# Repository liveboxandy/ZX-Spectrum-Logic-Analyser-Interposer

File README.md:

# ZX-Spectrum-Logic-Analyser-Interposer
Based on the design by HappyLittleDiodes but free form connections

Layout and connections completely redone so as to allow any logic signal on the edge connector or elsewhere to be connected to any Logic Analyser channel.

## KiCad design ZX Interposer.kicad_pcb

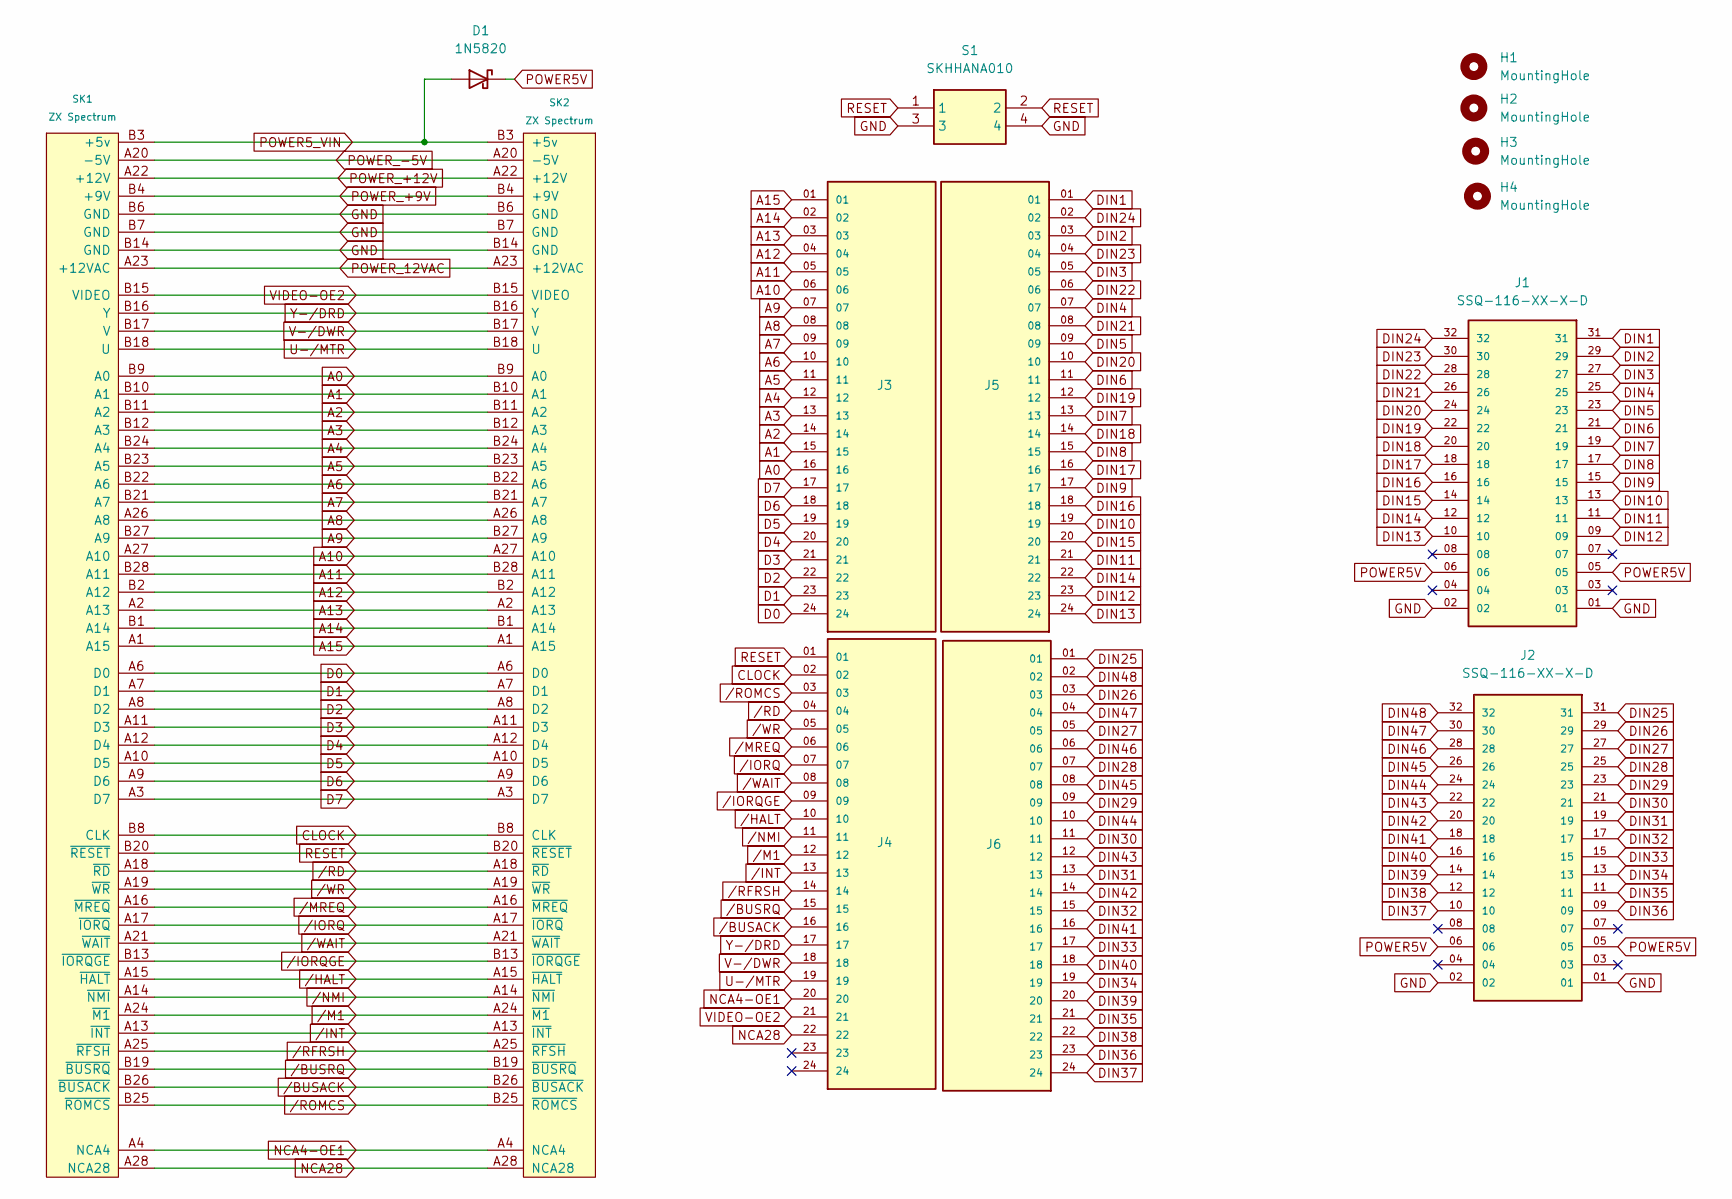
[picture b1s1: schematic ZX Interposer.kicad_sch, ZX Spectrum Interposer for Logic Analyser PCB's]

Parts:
D1: 1N5820; D_DO-201AD_P15.24mm_Horizontal
H1, H2, H3, H4: MountingHole; MountingHole_2.5mm
J1, J2: SSQ-116-XX-X-D; SAMTEC_SSQ-116-XX-X-D; PARTREV A
J3, J4, J5, J6: TSW-124-07-L-S; SAMTEC_TSW-124-07-L-S; PARTREV R
S1: SKHHANA010; Mouser Part Number 688-SKHHAN
SK1, SK2: ZX Spectrum; ZX_Spectrum_BUS_Edge_Connector Horizontal

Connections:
A0: J3.16, SK1.B9 (A0), SK2.B9 (A0)
A1: J3.15, SK1.B10 (A1), SK2.B10 (A1)
A2: J3.14, SK1.B11 (A2), SK2.B11 (A2)
A3: J3.13, SK1.B12 (A3), SK2.B12 (A3)
A4: J3.12, SK1.B24 (A4), SK2.B24 (A4)
A5: J3.11, SK1.B23 (A5), SK2.B23 (A5)
A6: J3.10, SK1.B22 (A6), SK2.B22 (A6)
A7: J3.09, SK1.B21 (A7), SK2.B21 (A7)
A8: J3.08, SK1.A26 (A8), SK2.A26 (A8)
A9: J3.07, SK1.B27 (A9), SK2.B27 (A9)
A10: J3.06, SK1.A27 (A10), SK2.A27 (A10)
A11: J3.05, SK1.B28 (A11), SK2.B28 (A11)
A12: J3.04, SK1.B2 (A12), SK2.B2 (A12)
A13: J3.03, SK1.A2 (A13), SK2.A2 (A13)
A14: J3.02, SK1.B1 (A14), SK2.B1 (A14)
A15: J3.01, SK1.A1 (A15), SK2.A1 (A15)
CLOCK: J4.02, SK1.B8 (CLK), SK2.B8 (CLK)
D0: J3.24, SK1.A6 (D0), SK2.A6 (D0)
D1: J3.23, SK1.A7 (D1), SK2.A7 (D1)
D2: J3.22, SK1.A8 (D2), SK2.A8 (D2)
D3: J3.21, SK1.A11 (D3), SK2.A11 (D3)
D4: J3.20, SK1.A12 (D4), SK2.A12 (D4)
D5: J3.19, SK1.A10 (D5), SK2.A10 (D5)
D6: J3.18, SK1.A9 (D6), SK2.A9 (D6)
D7: J3.17, SK1.A3 (D7), SK2.A3 (D7)
DIN1: J1.31, J5.01
DIN2: J1.29, J5.03
DIN3: J1.27, J5.05
DIN4: J1.25, J5.07
DIN5: J1.23, J5.09
DIN6: J1.21, J5.11
DIN7: J1.19, J5.13
DIN8: J1.17, J5.15
DIN9: J1.15, J5.17
DIN10: J1.13, J5.19
DIN11: J1.11, J5.21
DIN12: J1.09, J5.23
DIN13: J1.10, J5.24
DIN14: J1.12, J5.22
DIN15: J1.14, J5.20
DIN16: J1.16, J5.18
DIN17: J1.18, J5.16
DIN18: J1.20, J5.14
DIN19: J1.22, J5.12
DIN20: J1.24, J5.10
DIN21: J1.26, J5.08
DIN22: J1.28, J5.06
DIN23: J1.30, J5.04
DIN24: J1.32, J5.02
DIN25: J2.31, J6.01
DIN26: J2.29, J6.03
DIN27: J2.27, J6.05
DIN28: J2.25, J6.07
DIN29: J2.23, J6.09
DIN30: J2.21, J6.11
DIN31: J2.19, J6.13
DIN32: J2.17, J6.15
DIN33: J2.15, J6.17
DIN34: J2.13, J6.19
DIN35: J2.11, J6.21
DIN36: J2.09, J6.23
DIN37: J2.10, J6.24
DIN38: J2.12, J6.22
DIN39: J2.14, J6.20
DIN40: J2.16, J6.18
DIN41: J2.18, J6.16
DIN42: J2.20, J6.14
DIN43: J2.22, J6.12
DIN44: J2.24, J6.10
DIN45: J2.26, J6.08
DIN46: J2.28, J6.06
DIN47: J2.30, J6.04
DIN48: J2.32, J6.02
GND: J1.01, J1.02, J2.01, J2.02, S1.3, S1.4, SK1.B6 (GND), SK1.B7 (GND), SK1.B14 (GND), SK2.B6 (GND), SK2.B7 (GND), SK2.B14 (GND)
NCA4-OE1: J4.20, SK1.A4 (NCA4), SK2.A4 (NCA4)
NCA28: J4.22, SK1.A28 (NCA28), SK2.A28 (NCA28)
POWER5V: D1.1 (K), J1.05, J1.06, J2.05, J2.06
POWER5_VIN: D1.2 (A), SK1.B3 (+5v), SK2.B3 (+5v)
POWER_12VAC: SK1.A23 (+12VAC), SK2.A23 (+12VAC)
POWER_+9V: SK1.B4 (+9V), SK2.B4 (+9V)
POWER_+12V: SK1.A22 (+12V), SK2.A22 (+12V)
POWER_-5V: SK1.A20 (-5V), SK2.A20 (-5V)
RESET: J4.01, S1.1, S1.2, SK1.B20 (~RESET), SK2.B20 (~RESET)
U-/MTR: J4.19, SK1.B18 (U), SK2.B18 (U)
V-/DWR: J4.18, SK1.B17 (V), SK2.B17 (V)
VIDEO-OE2: J4.21, SK1.B15 (VIDEO), SK2.B15 (VIDEO)
Y-/DRD: J4.17, SK1.B16 (Y), SK2.B16 (Y)
/BUSACK: J4.16, SK1.B26 (~BUSACK), SK2.B26 (~BUSACK)
/BUSRQ: J4.15, SK1.B19 (~BUSRQ), SK2.B19 (~BUSRQ)
/HALT: J4.10, SK1.A15 (~HALT), SK2.A15 (~HALT)
/INT: J4.13, SK1.A13 (~INT), SK2.A13 (~INT)
/IORQ: J4.07, SK1.A17 (~IORQ), SK2.A17 (~IORQ)
/IORQGE: J4.09, SK1.B13 (~IORQGE), SK2.B13 (~IORQGE)
/M1: J4.12, SK1.A24 (~M1), SK2.A24 (~M1)
/MREQ: J4.06, SK1.A16 (~MREQ), SK2.A16 (~MREQ)
/NMI: J4.11, SK1.A14 (~NMI), SK2.A14 (~NMI)
/RD: J4.04, SK1.A18 (~RD), SK2.A18 (~RD)
/RFRSH: J4.14, SK1.A25 (~RFSH), SK2.A25 (~RFSH)
/ROMCS: J4.03, SK1.B25 (~ROMCS), SK2.B25 (~ROMCS)
/WAIT: J4.08, SK1.A21 (~WAIT), SK2.A21 (~WAIT)
/WR: J4.05, SK1.A19 (~WR), SK2.A19 (~WR)

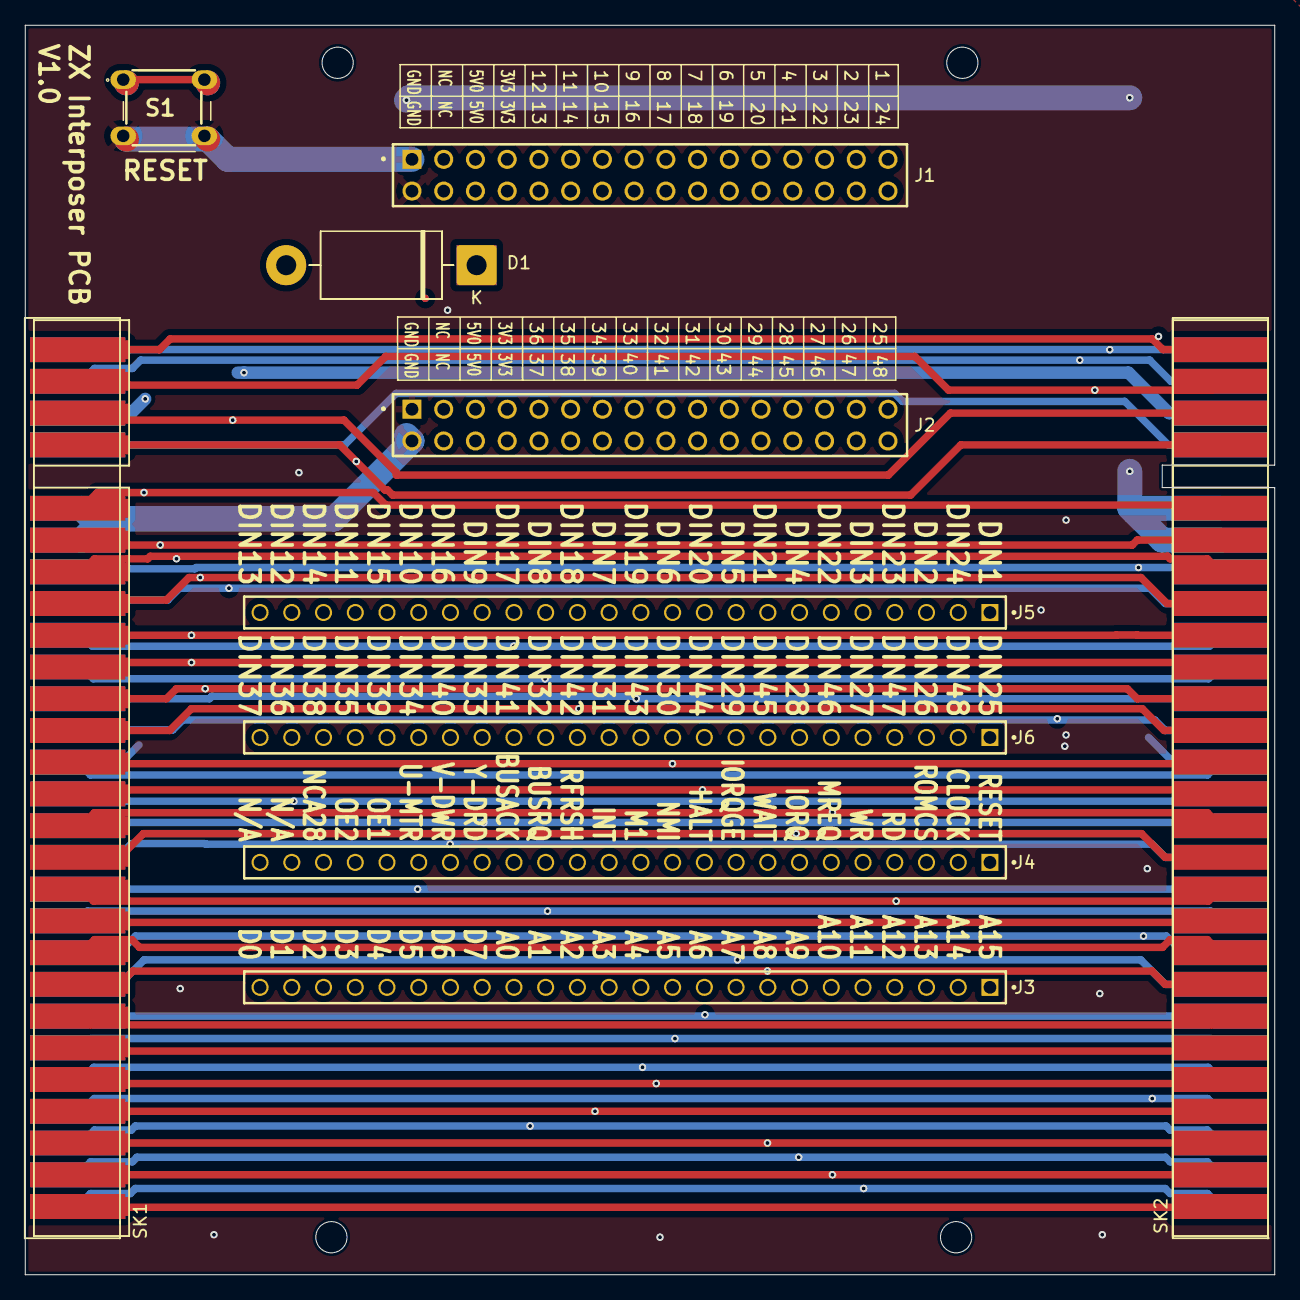
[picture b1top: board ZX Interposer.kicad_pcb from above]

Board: 4 copper layers, 100.0 x 100.0 mm, 14 parts (0 on the bottom side), 101 nets.

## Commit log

2026-01-22 Update README with new layout and connection details
    Redesigned layout and connections for flexibility in signal connections.
